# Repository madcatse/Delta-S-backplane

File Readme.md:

# Delta-S Backplane / Бекплейн для «Дельта‑С»

## RU

### Что это

Этот проект — печатная плата бекплейна для компьютера «Дельта‑С» (совместимая ZX‑архитектура), которая расширяет системную шину и упрощает подключение периферии.

Плата предназначена для:
- подключения нескольких дополнительных устройств через разъёмы СНП;
- вывода системных сигналов в формате ZX BUS / Nemo Bus;
- питания подключённых устройств либо от компьютера, либо от внешнего источника +5 В с аппаратным выбором источника.

---

### Ключевые возможности

- **4 слота СНП для модулей расширения** (разъёмы J2–J5).
- **Системный вход от компьютера «Дельта‑С»** через угловой СНП‑разъём (J1).
- **Выводы на внешние шины**:
  - J6 — разъём ZX‑BUS;
  - J7 — edge‑разъём формата ZX Spectrum bus.
- **Два варианта питания +5 В**:
  - внутреннее (от хоста «Дельта‑С»);
  - внешнее через barrel‑jack (J8) / штыревой разъём питания (J9).
- **Переключение источника питания джампером JP1**:
  - `1–2` — internal +5V power;
  - `2–3` — external power.
- **Фильтрация питания на плате**: C1 (1000 µF) + C2 (0.1 µF).

---

### Разъёмы и элементы

| Обозначение | Назначение |
|---|---|
| J2, J3, J4, J5 | Слоты СНП для плат расширения |
| J1 | Входной разъём к компьютеру «Дельта‑С» (магистраль бекплейна) |
| J6 | Вывод шины ZX‑BUS |
| J7 | Edge‑разъём шины (ZX Spectrum bus format) |
| J8 | Внешнее питание через DC barrel jack |
| J9 | Штыревой разъём питания/сервисный вывод (+5V/GND) |
| JP1 | Выбор источника +5 В (внутренний/внешний) |
| C1, C2 | Сглаживание и развязка питания |

> Важно: перед установкой `JP1 = 2–3` убедитесь, что внешний источник стабилизирован и соответствует **+5 В DC**.

---

### Что внутри проекта

- `deltas_backplane.kicad_sch` — электрическая схема.
- `deltas_backplane.kicad_pcb` — топология печатной платы.
- `gerbers/` — набор Gerber/Excellon для производства.
- `Libs/` — локальные библиотеки символов, футпринтов и 3D‑моделей.

Проект выполнен в формате KiCad 9‑совместимых файлов.

---

### Производство и сборка

1. Откройте `deltas_backplane.kicad_pcb` в KiCad и визуально проверьте ревизию/маркировки.
2. Используйте готовые файлы из `gerbers/` или сгенерируйте свой комплект под нужную ревизию.
3. После пайки **сначала** установите джампер питания JP1 в нужный режим, **затем** подключайте периферию.
4. При использовании внешнего источника избегайте одновременной «жёсткой» подпитки +5 В от нескольких источников.

---

### Совместимость и контекст

По структуре сигналов проект рассчитан на ZX‑совместимую экосистему «Дельта‑С» с выводом шины в форматах ZX BUS / Nemo Bus. Фактическая совместимость конкретных периферийных устройств зависит от их электрических требований, распиновки и поведения управляющих сигналов.

---

## EN

### What this project is

This repository contains a backplane PCB for the **Delta‑S** computer (ZX‑compatible ecosystem). The board extends the system bus and makes peripheral expansion easier.

It is designed to:
- connect multiple expansion devices through SNP connectors;
- expose system signals in **ZX BUS / Nemo Bus** form factors;
- power attached devices either from the host computer or from an external +5 V source (hardware selectable).

---

### Key features

- **4 SNP expansion slots** (J2–J5).
- **Host connection to Delta‑S** via angled SNP connector (J1).
- **External bus outputs**:
  - J6 — ZX‑BUS connector;
  - J7 — edge connector in ZX Spectrum bus format.
- **Dual +5 V power options**:
  - internal (from the Delta‑S host);
  - external via barrel jack (J8) / header connector (J9).
- **JP1 power source selection**:
  - `1–2` — internal +5V power;
  - `2–3` — external power.
- **Onboard power filtering**: C1 (1000 µF) + C2 (0.1 µF).

---

### Connectors and parts

| Designator | Function |
|---|---|
| J2, J3, J4, J5 | SNP slots for expansion cards |
| J1 | Upstream connector to Delta‑S host bus |
| J6 | ZX‑BUS output |
| J7 | Edge bus connector (ZX Spectrum format) |
| J8 | External power input (DC barrel jack) |
| J9 | Pin header for power/service (+5V/GND) |
| JP1 | +5 V source select (internal/external) |
| C1, C2 | Bulk/decoupling capacitors |

> Important: before setting `JP1 = 2–3`, verify that your external PSU is properly regulated at **+5 V DC**.

---

### Repository contents

- `deltas_backplane.kicad_sch` — schematic.
- `deltas_backplane.kicad_pcb` — board layout.
- `gerbers/` — manufacturing Gerber/Excellon files.
- `Libs/` — local symbols, footprints, and 3D models.

The project uses KiCad file formats compatible with KiCad 9 workflows.

---

### Manufacturing and bring‑up notes

1. Open `deltas_backplane.kicad_pcb` in KiCad and confirm board revision/silkscreen.
2. Use the prepared set in `gerbers/` (or regenerate for your target revision).
3. After assembly, set JP1 to the required power mode **before** attaching expansion cards.
4. When using external power, avoid hard‑tying multiple +5 V sources without proper isolation.

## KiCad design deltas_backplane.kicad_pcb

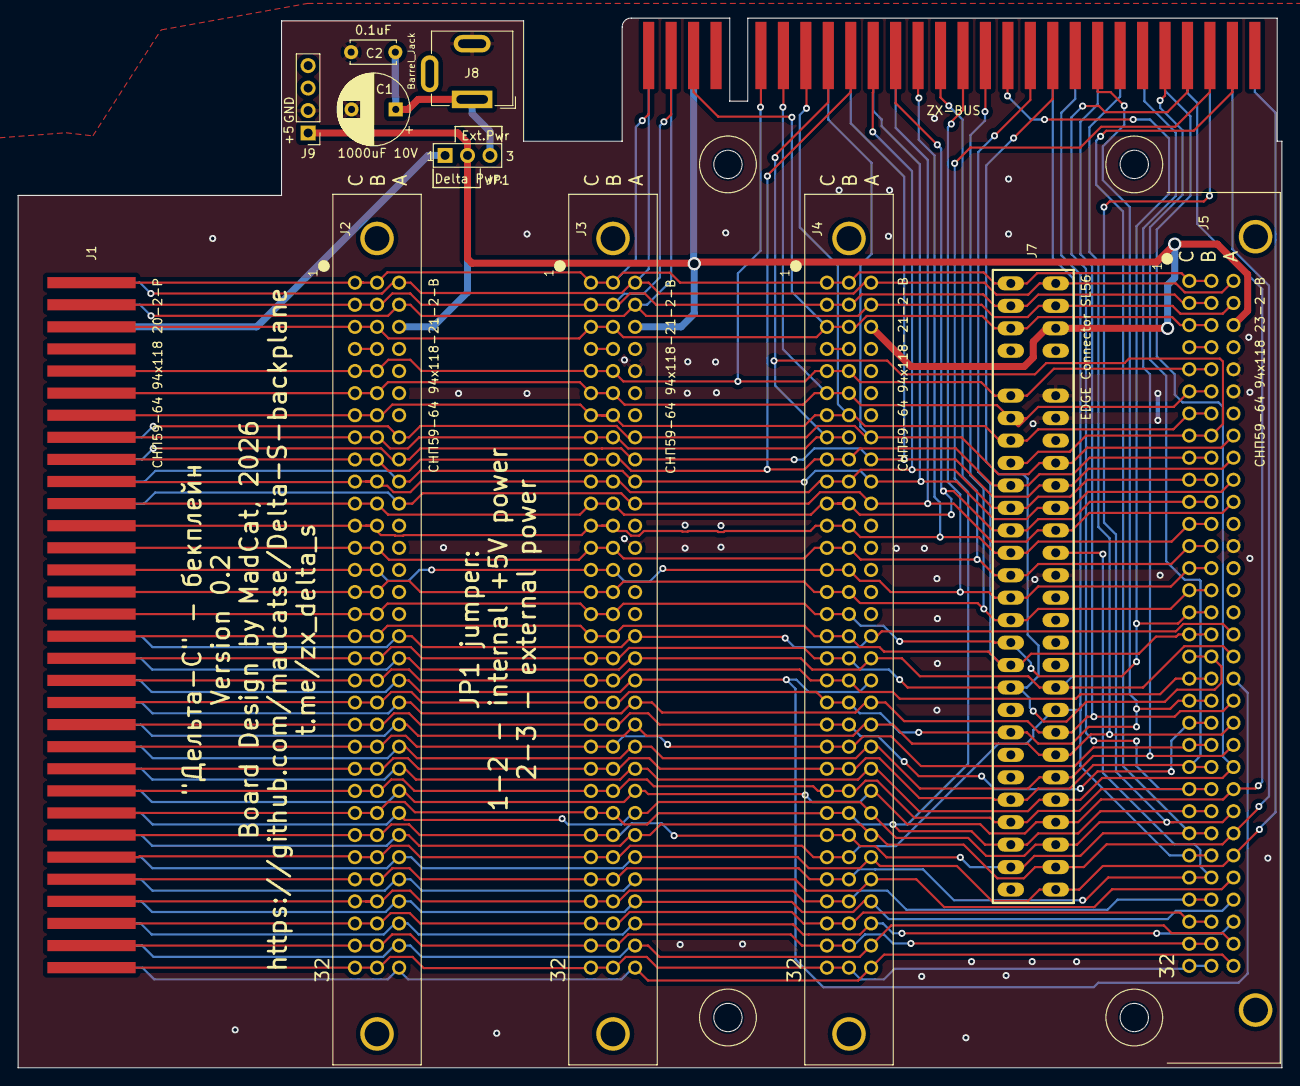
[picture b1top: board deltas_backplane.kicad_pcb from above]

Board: 2 copper layers, 143.0 x 118.8 mm, 16 parts (0 on the bottom side), 57 nets.

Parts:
C1: 1000uF 10V; CP_Radial_D8.0mm_P5.00mm
C2: 0.1uF; C_Disc_D5.0mm_W2.5mm_P5.00mm
J1: СНП59-64 94х118 20-2-Р; snp_straight
J2, J3, J4: СНП59-64 94х118-21-2-В; snp59_96_male_straight
J5: СНП59-64 94х118 23-2-В; snp59_96_female_angle_3
J6: ZX-BUS; ZX SPECTRUM EDGE CONNECTOR (HORIZONTAL)
J7: EDGE Connector SL56; Spectrum_edge_slot_FIXED
J8: Barrel_Jack; BarrelJack_GCT_DCJ200-10-A_Horizontal
J9: Conn_01x04; PinHeader_1x04_P2.54mm_Vertical
JP1: Jumper_3_Open; PinHeader_1x03_P2.54mm_Vertical
M31, M31#2, M31#3, M31#4: MountingHole_3.2mm_M3

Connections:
5V_connector: J2.35 ("+5"), J3.35 ("+5"), J4.35 ("+5"), J5.35 ("+5"), J6.31 (+5V), J7.31 (+5V), J9.1, JP1.2 (C)
+5V: J1.35 ("+5"), JP1.1 (A)
A0: J1.40 (A0), J2.40 (A0), J3.40 (A0), J4.40 (A0), J5.40 (A0), J6.37 (A0), J7.37 (A0)
A1: J1.41 (A1), J2.41 (A1), J3.41 (A1), J4.41 (A1), J5.41 (A1), J6.38 (A1), J7.38 (A1)
A2: J1.42 (A2), J2.42 (A2), J3.42 (A2), J4.42 (A2), J5.42 (A2), J6.39 (A2), J7.39 (A2)
A3: J1.43 (A3), J2.43 (A3), J3.43 (A3), J4.43 (A3), J5.43 (A3), J6.40 (A3), J7.40 (A3)
A4: J1.55 (A4), J2.55 (A4), J3.55 (A4), J4.55 (A4), J5.55 (A4), J6.52 (A4), J7.52 (A4)
A5: J1.54 (A5), J2.54 (A5), J3.54 (A5), J4.54 (A5), J5.54 (A5), J6.51 (A5), J7.51 (A5)
A6: J1.53 (A6), J2.53 (A6), J3.53 (A6), J4.53 (A6), J5.53 (A6), J6.50 (A6), J7.50 (A6)
A7: J1.52 (A7), J2.52 (A7), J3.52 (A7), J4.52 (A7), J5.52 (A7), J6.49 (A7), J7.49 (A7)
A8: J1.25 (A8), J2.25 (A8), J3.25 (A8), J4.25 (A8), J5.25 (A8), J6.26 (A8), J7.26 (A8)
A9: J1.58 (A9), J2.58 (A9), J3.58 (A9), J4.58 (A9), J5.58 (A9), J6.55 (A9), J7.55 (A9)
A10: J1.26 (A10), J2.26 (A10), J3.26 (A10), J4.26 (A10), J5.26 (A10), J6.27 (A10), J7.27 (A10)
A11: J1.59 (A11), J2.59 (A11), J3.59 (A11), J4.59 (A11), J5.59 (A11), J6.56 (A11), J7.56 (A11)
A12: J1.34 (A12), J2.34 (A12), J3.34 (A12), J4.34 (A12), J5.34 (A12), J6.30 (A12), J7.30 (A12)
A13: J1.2 (A13), J2.2 (A13), J3.2 (A13), J4.2 (A13), J5.2 (A13), J6.2 (A13), J7.2 (A13)
A14: J1.33 (A14), J2.33 (A14), J3.33 (A14), J4.33 (A14), J5.33 (A14), J6.29 (A14), J7.29 (A14)
A15: J1.1 (A15), J2.1 (A15), J3.1 (A15), J4.1 (A15), J5.1 (A15), J6.1 (A15), J7.1 (A15)
A19_SNP: J1.51 (BD1), J2.51 (BD1), J3.51 (BD1), J4.51 (BD1), J5.51 (BD1)
A28_SNP: J1.60 (P5), J2.60 (P5), J3.60 (P5), J4.60 (P5), J5.60 (P5)
A29_SNP: J1.61 (BD3), J2.61 (BD3), J3.61 (BD3), J4.61 (BD3), J5.61 (BD3)
A30_SNP: J1.62 (BD5), J2.62 (BD5), J3.62 (BD5), J4.62 (BD5), J5.62 (BD5)
A31_SNP: J1.63 (BD6), J2.63 (BD6), J3.63 (BD6), J4.63 (BD6), J5.63 (BD6)
B19_SNP: J1.19 (BD2), J2.19 (BD2), J3.19 (BD2), J4.19 (BD2), J5.19 (BD2)
B21_SNP: J1.21 (P1), J2.21 (P1), J3.21 (P1), J4.21 (P1), J5.21 (P1)
B22_SNP: J1.22 (P2), J2.22 (P2), J3.22 (P2), J4.22 (P2), J5.22 (P2)
B28_SNP: J1.28 (P4), J2.28 (P4), J3.28 (P4), J4.28 (P4), J5.28 (P4), J7.41 (NC)
B29_SNP: J1.29 (P5), J2.29 (P5), J3.29 (P5), J4.29 (P5), J5.29 (P5)
B30_SNP: J1.30 (BD4), J2.30 (BD4), J3.30 (BD4), J4.30 (BD4), J5.30 (BD4)
B31_SNP: J1.31 (BD0), J2.31 (BD0), J3.31 (BD0), J4.31 (BD0), J5.31 (BD0)
B32_SNP: J1.32 (BD7), J2.32 (BD7), J3.32 (BD7), J4.32 (BD7), J5.32 (BD7)
BUSY: J1.64 (ГТ), J2.64 (ГТ), J3.64 (ГТ), J4.64 (ГТ), J5.64 (ГТ)
D0: J1.5 (D0), J2.5 (D0), J3.5 (D0), J4.5 (D0), J5.5 (D0), J6.6 (D0), J7.6 (D0)
D1: J1.6 (D1), J2.6 (D1), J3.6 (D1), J4.6 (D1), J5.6 (D1), J6.7 (D1), J7.7 (D1)
D2: J1.7 (D2), J2.7 (D2), J3.7 (D2), J4.7 (D2), J5.7 (D2), J6.8 (D2), J7.8 (D2)
D3: J1.10 (D3), J2.10 (D3), J3.10 (D3), J4.10 (D3), J5.10 (D3), J6.11 (D3), J7.11 (D3)
D4: J1.11 (D4), J2.11 (D4), J3.11 (D4), J4.11 (D4), J5.11 (D4), J6.12 (D4), J7.12 (D4)
D5: J1.9 (D5), J2.9 (D5), J3.9 (D5), J4.9 (D5), J5.9 (D5), J6.10 (D5), J7.10 (D5)
D6: J1.8 (D6), J2.8 (D6), J3.8 (D6), J4.8 (D6), J5.8 (D6), J6.9 (D6), J7.9 (D6)
D7: J1.3 (D7), J2.3 (D7), J3.3 (D7), J4.3 (D7), J5.3 (D7), J6.3 (D7), J7.3 (D7)
GND: C1.2, C2.2, J1.37 (Общий), J1.38 (Общий), J1.45 (Общий), J2.37 (Общий), J2.38 (Общий), J2.45 (Общий), J3.37 (Общий), J3.38 (Общий), J3.45 (Общий), J4.37 (Общий), J4.38 (Общий), J4.45 (Общий), J5.37 (Общий), J5.38 (Общий), J5.45 (Общий), J6.34 (GND), J6.35 (GND), J6.42 (GND), J7.34 (GND), J7.35 (GND), J7.42 (GND), J8.2, J9.2
M1L: J1.23 (М1), J2.23 (М1), J3.23 (М1), J4.23 (М1), J5.23 (М1), J6.24 (M1), J7.24 (M1)
unnamed: C1.1, C2.1, J8.1, JP1.3 (B)
STROBL: J1.49 (СТР), J2.49 (СТР), J3.49 (СТР), J4.49 (СТР), J5.49 (СТР)
ВУL: J1.16 (ВУ), J2.16 (ВУ), J3.16 (ВУ), J4.16 (ВУ), J5.16 (ВУ), J6.17 (IORQ), J7.17 (IORQ)
ЗАПРШL: J1.50 (ЗАПРШ), J2.50 (ЗАПРШ), J3.50 (ЗАПРШ), J4.50 (ЗАПРШ), J5.50 (ЗАПРШ), J6.47 (BUSRQ), J7.47 (BUSRQ)
ЗПL: J1.18 (ЗП), J2.18 (ЗП), J3.18 (ЗП), J4.18 (ЗП), J5.18 (ЗП), J6.19 (WR), J7.19 (WR)
НПРL: J1.13 (НПР), J2.13 (НПР), J3.13 (НПР), J4.13 (НПР), J5.13 (НПР), J6.14 (NMI), J7.14 (NMI)
ОЖИДL: J1.20 (ОЖИД), J2.20 (ОЖИД), J3.20 (ОЖИД), J4.20 (ОЖИД), J5.20 (ОЖИД), J6.21 (WAIT), J7.21 (WAIT)
ОЗУL: J1.15 (ОЗУ), J2.15 (ОЗУ), J3.15 (ОЗУ), J4.15 (ОЗУ), J5.15 (ОЗУ), J6.16 (MREQ), J7.16 (MREQ)
ПЗШL: J1.57 (ПЗШ), J2.57 (ПЗШ), J3.57 (ПЗШ), J4.57 (ПЗШ), J5.57 (ПЗШ), J6.54 (BUSACK), J7.54 (BUSACK)
ПРL: J1.12 (ПР), J2.12 (ПР), J3.12 (ПР), J4.12 (ПР), J5.12 (ПР), J6.13 (INT), J7.13 (INT)
РГНL: J1.24 (РГН), J2.24 (РГН), J3.24 (РГН), J4.24 (РГН), J5.24 (РГН), J6.25 (RFSH), J7.25 (RFSH)
СБРОСL: J1.27 (СБРОС), J2.27 (СБРОС), J3.27 (СБРОС), J4.27 (СБРОС), J5.27 (СБРОС), J6.48 (RESET), J7.48 (RESET)
СТОПL: J1.14 (СТОП), J2.14 (СТОП), J3.14 (СТОП), J4.14 (СТОП), J5.14 (СТОП), J6.15 (HALT), J7.15 (HALT)
ЧТL: J1.17 (ЧТ), J2.17 (ЧТ), J3.17 (ЧТ), J4.17 (ЧТ), J5.17 (ЧТ), J6.18 (RD), J7.18 (RD)
ЧТПЗУL: J1.56 (БЛК_ПЗУ), J2.56 (БЛК_ПЗУ), J3.56 (БЛК_ПЗУ), J4.56 (БЛК_ПЗУ), J5.56 (БЛК_ПЗУ), J6.53 (ROMCS), J7.53 (ROMCS)

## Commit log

2023-10-02 Initial upload
2023-10-03 Power fix
2023-10-03 03.10.2023 update
2023-10-10 Gerbers upload
2023-10-10 Small update (0.1.1)
2026-02-25 Version 0.2 upload
2026-02-25 Pics
